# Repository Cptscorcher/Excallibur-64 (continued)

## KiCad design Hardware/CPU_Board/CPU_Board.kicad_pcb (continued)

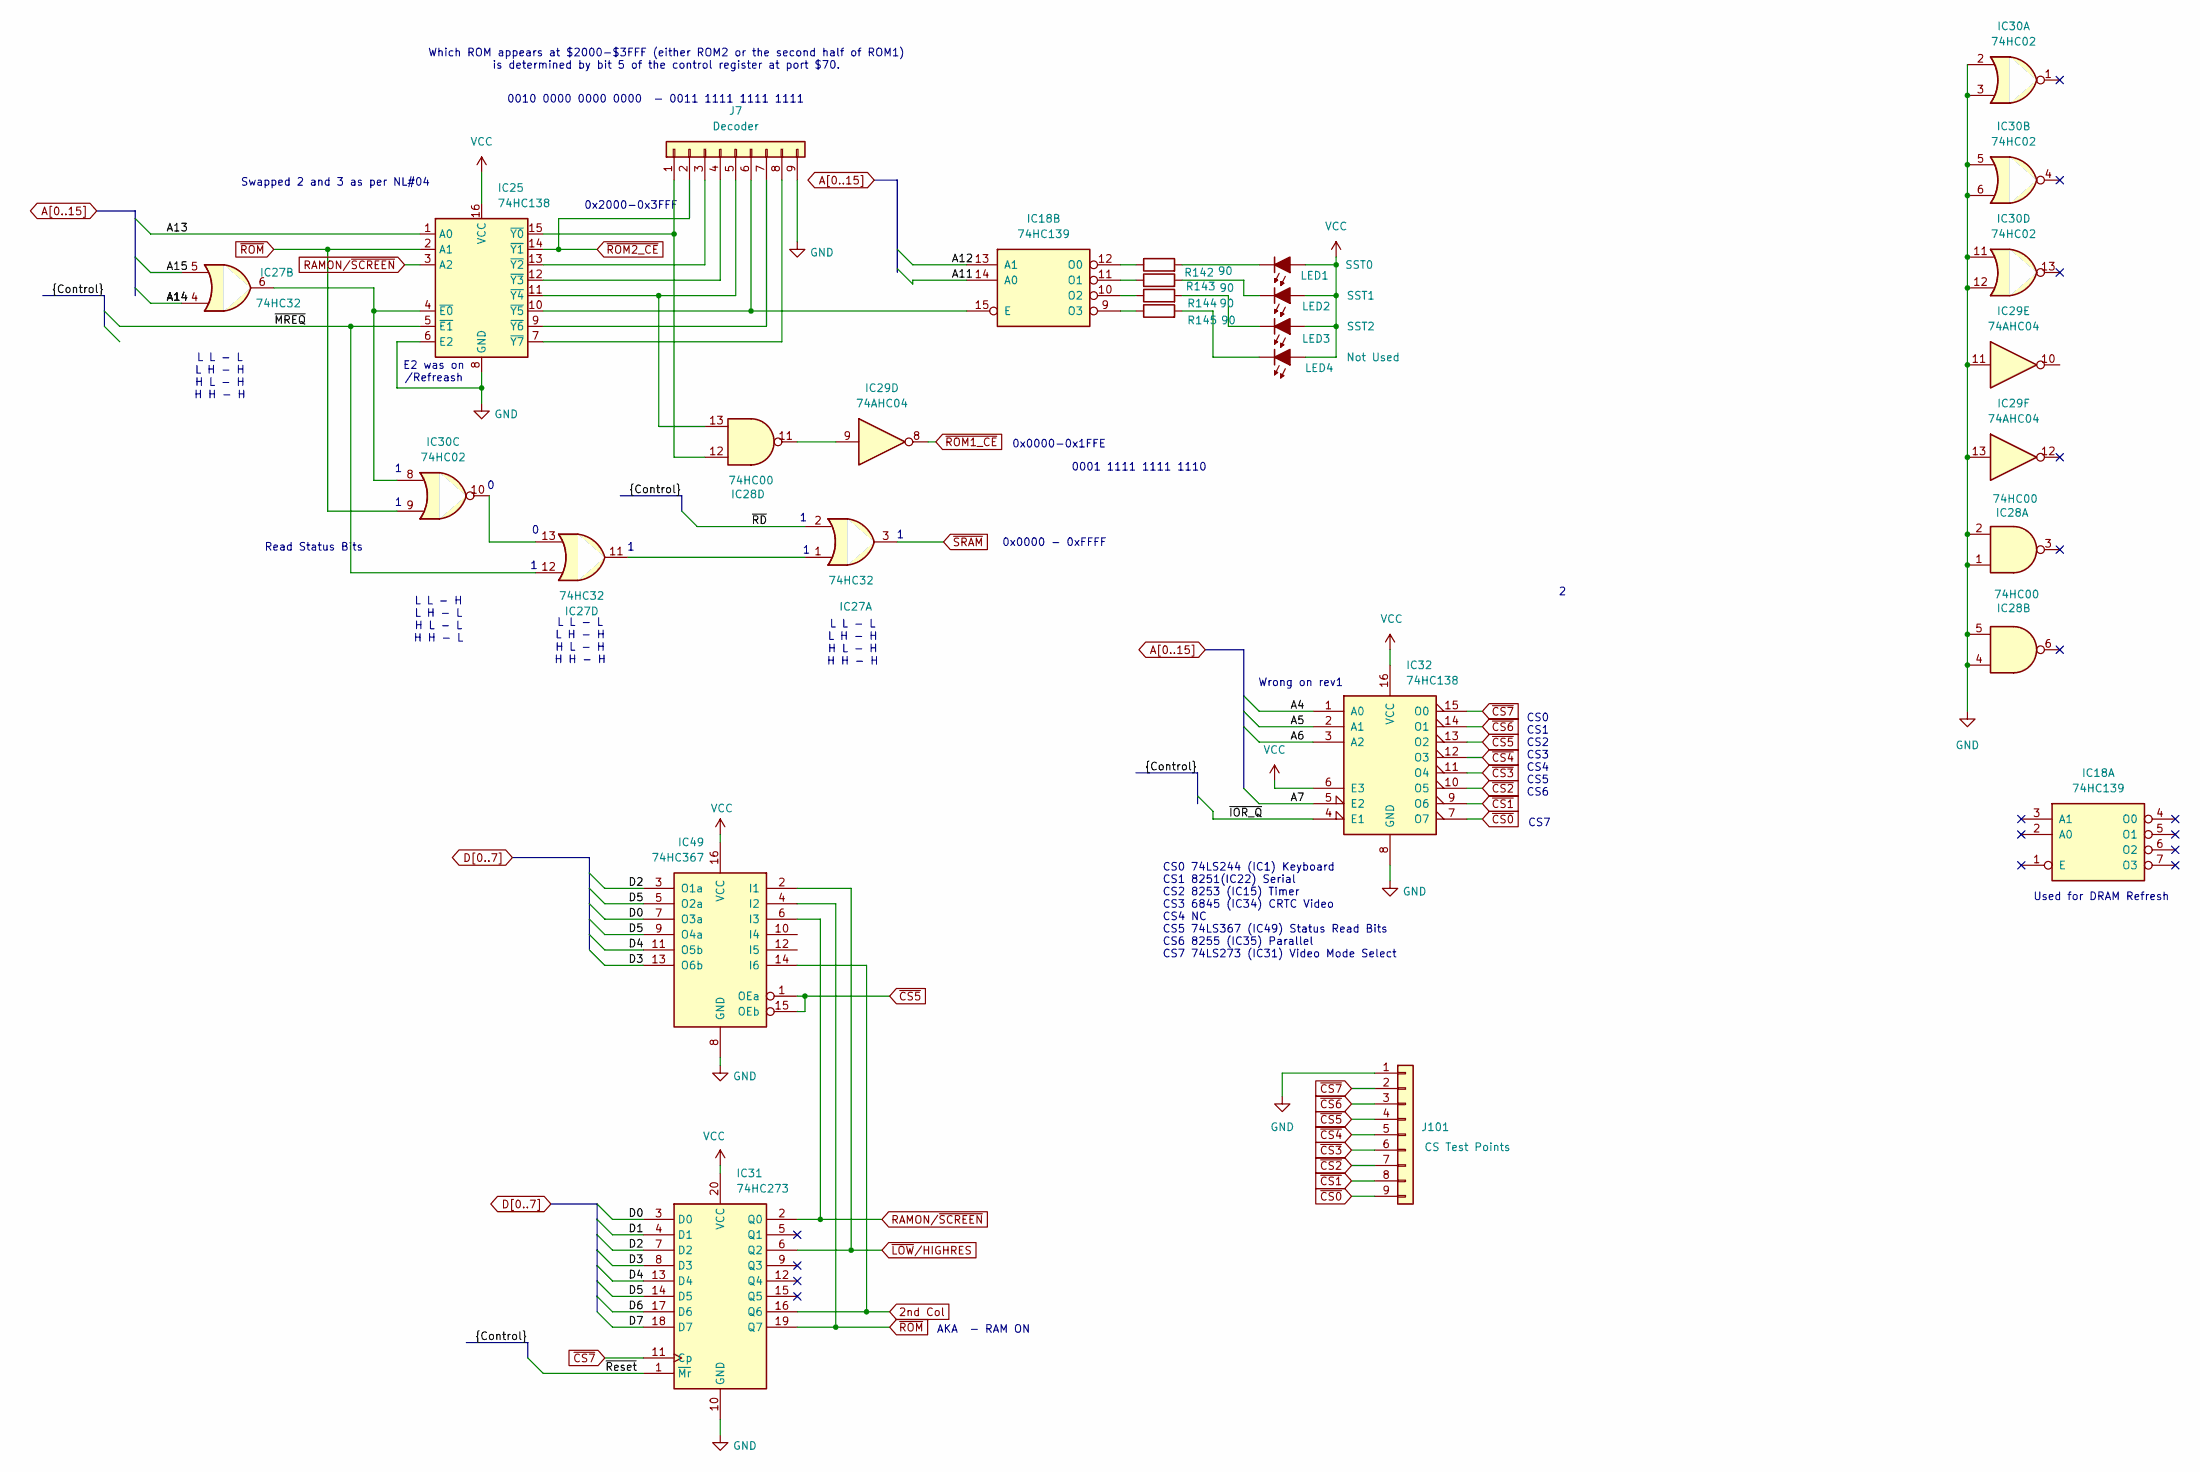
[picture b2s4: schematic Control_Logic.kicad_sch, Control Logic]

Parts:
IC18: 74HC139; DIP-16_W7.62mm_Socket_LongPads
IC25: 74HC138; DIP-16_W7.62mm_LongPads
IC27: 74HC32; DIP-14_W7.62mm_LongPads
IC28: 74HC00; DIP-14_W7.62mm_LongPads
IC29: 74AHC04; DIP-14_W7.62mm_Socket_LongPads
IC30: 74HC02; DIP-14_W7.62mm_LongPads
IC31: 74HC273; DIP-20_W7.62mm_Socket
IC32: 74HC138; DIP-16_W7.62mm_Socket_LongPads
IC49: 74HC367; DIP-16_W7.62mm_Socket_LongPads
J7: Decoder; PinHeader_1x09_P2.54mm_Vertical
J101: CS Test Points; PinHeader_1x09_P2.54mm_Vertical
LED1: SST0; LED_1206_3216Metric
LED2: SST1; LED_1206_3216Metric
LED3: SST2; LED_1206_3216Metric
LED4: Not Used; LED_1206_3216Metric
R142, R143, R144, R145: 90; R_1206_3216Metric_Pad1.30x1.75mm_HandSolder

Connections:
2nd Col: IC31.16 (Q6), IC49.14 (I6)
/Control_logic/~IOR_Q: IC32.4 (E1)
/Control_logic/~MREQ: IC25.5 (~E1), IC27.12
/Control_logic/~RD: IC27.2
/Control_logic/~Reset: IC31.1 (~Mr)
A4: IC32.1 (A0); also elsewhere on the board
A5: IC32.2 (A1); also elsewhere on the board
A6: IC32.3 (A2); also elsewhere on the board
A7: IC32.5 (E2); also elsewhere on the board
A11: IC18.14 (A0); also elsewhere on the board
A12: IC18.13 (A1); also elsewhere on the board
A13: IC25.1 (A0); also elsewhere on the board
A15: IC27.5; also elsewhere on the board
D0: IC31.3 (D0), IC49.7 (O3a); also elsewhere on the board
D1: IC31.4 (D1); also elsewhere on the board
D2: IC31.7 (D2), IC49.3 (O1a); also elsewhere on the board
D3: IC31.8 (D3), IC49.13 (O6b); also elsewhere on the board
D4: IC31.13 (D4), IC49.11 (O5b); also elsewhere on the board
D5: IC31.14 (D5), IC49.5 (O2a), IC49.9 (O4a); also elsewhere on the board
D6: IC31.17 (D6); also elsewhere on the board
D7: IC31.18 (D7); also elsewhere on the board
unnamed: IC18.15 (E), IC25.10 (~Y5), J7.6
unnamed: IC18.12 (O0), R142.1
unnamed: IC18.11 (O1), R143.1
unnamed: IC18.10 (O2), R144.1
unnamed: IC18.9 (O3), R145.1
unnamed: IC25.4 (~E0), IC27.6, IC30.8
unnamed: IC25.15 (~Y0), IC28.12, J7.1
unnamed: IC25.13 (~Y2), J7.3
unnamed: IC25.12 (~Y3), J7.4
unnamed: IC25.11 (~Y4), IC28.13, J7.5
unnamed: IC25.9 (~Y6), J7.7
unnamed: IC25.7 (~Y7), J7.8
unnamed: IC27.1, IC27.11
unnamed: IC27.13, IC30.10
unnamed: IC28.11, IC29.9
unnamed: LED1.1 (K), R142.2
unnamed: LED2.1 (K), R143.2
unnamed: LED3.1 (K), R144.2
unnamed: LED4.1 (K), R145.2
RAMON/~SCREEN: IC25.3 (A2), IC31.2 (Q0), IC49.6 (I3); also elsewhere on the board
VCC: IC25.16 (VCC), IC31.20 (VCC), IC32.6 (E3), IC32.16 (VCC), IC49.16 (VCC), LED1.2 (A), LED2.2 (A), LED3.2 (A), LED4.2 (A); also elsewhere on the board
~CS0: IC32.7 (O7), J101.9; also elsewhere on the board
~CS1: IC32.9 (O6), J101.8; also elsewhere on the board
~CS2: IC32.10 (O5), J101.7; also elsewhere on the board
~CS3: IC32.11 (O4), J101.6
~CS4: IC32.12 (O3), J101.5
~CS5: IC32.13 (O2), IC49.1 (OEa), IC49.15 (OEb), J101.4
~CS6: IC32.14 (O1), J101.3; also elsewhere on the board
~CS7: IC31.11 (Cp), IC32.15 (O0), J101.2
~LOW/HIGHRES: IC31.6 (Q2), IC49.2 (I1)
~ROM1_CE: IC29.8; also elsewhere on the board
~ROM2_CE: IC25.14 (~Y1), J7.2; also elsewhere on the board
~ROM: IC25.2 (A1), IC30.9, IC31.19 (Q7), IC49.4 (I2)
~SRAM: IC27.3; also elsewhere on the board

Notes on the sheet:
Read Status Bits
Wrong on rev1
L L - H L H - L H L - L H H - L
L L - L L H - H H L - H H H - H
0001 1111 1111 1110
0x0000-0x1FFE
Used for DRAM Refresh
0x0000 - 0xFFFF
E2 was on /Refreash
CS0 74LS244 (IC1) Keyboard CS1 8251(IC22) Serial CS2 8253 (IC15) Timer CS3 6845 (IC34) CRTC Video CS4 NC CS5 74LS367 (IC49) Status Read Bits CS6 8255 (IC35) Parallel CS7 74LS273 (IC31) Video Mode Select
Swapped 2 and 3 as per NL#04
CS0 CS1 CS2 CS3 CS4 CS5 CS6
CS7
Which ROM appears at $2000-$3FFF (either ROM2 or the second half of ROM1) is determined by bit 5 of the control register at port $70.
AKA - RAM ON
0010 0000 0000 0000 - 0011 1111 1111 1111
0x2000-0x3FFF

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
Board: 2 copper layers, 150 parts (0 on the bottom side), 180 nets, no tracks yet.

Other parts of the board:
REF01, REF02, REF04, REF05, REF06: MountingHole_3.2mm_M3_DIN965_Pad
U101#2: 74AHCU04; DIP-14_W7.62mm_Socket_LongPads

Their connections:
/Power_Reset/~RESET: U101#2.10; also elsewhere on the board
VCC: U101#2.14 (VCC); also elsewhere on the board

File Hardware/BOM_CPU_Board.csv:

"Reference","Value","Qty","DNP"
"C7,C121,C123,C124,C125,C126","1uF","6",""
"C19,C101","4.7uF","2",""
"C25","56nF","1",""
"C26","10uF","1",""
"C102,C103,C104,C105,C106,C108,C109,C111,C112,C113,C114,C115,C116,C117,C118,C119,C120,C129,C130,C131","10nf","20",""
"C107,C128","33p","2",""
"C110","1000uF","1",""
"C122","100uF","1",""
"C127","100pf","1",""
"D1,D2,D3,D4,D5,D6,D7,D8,D21,D22,D104","1N4148","11",""
"D101","5v","1",""
"D102","1N4448","1",""
"D103","12v","1",""
"DZ101","BZX79-B2V4","1",""
"IC1","74HCT244","1",""
"IC15","8253","1",""
"IC16","Z84C00","1",""
"IC18","74HC139","1",""
"IC22","8251","1",""
"IC25,IC32","74HC138","2",""
"IC27","74HC32","1",""
"IC28","74HC00","1",""
"IC29","74HC04","1",""
"IC30","74HC02","1",""
"IC31","74HC273","1",""
"IC35","82C55A","1",""
"IC42","LM348N","1",""
"IC49","74HC367","1",""
"IC54","74HC123","1",""
"IC56","74HC161","1",""
"IC102","MAX232","1",""
"IC110","SST39SF010","1",""
"IC111","HM62256ALSP","1",""
"J3","Ext Clk","1",""
"J4","Expansion","1",""
"J7","Decoder","1",""
"J101","CS Test Points","1",""
"J102","Tx","1",""
"J103","Rx","1",""
"J104","SPEAKER (AUDIO)","1",""
"J105","TTL Serial","1",""
"J107","Power In","1",""
"J108","CASSETTE","1",""
"J109","RTS - DSR","1",""
"J110","PARALLEL OUTPUT PORT","1",""
"J111","Keyboard","1",""
"J112","Serial","1",""
"LED1","SST0","1",""
"LED2","SST1","1",""
"LED3","SST2","1",""
"LED4","Not Used","1",""
"LED101,LED103","Red","2",""
"LED102,LED104","Green","2",""
"Q1,Q102","BC548","2",""
"Q101","2N2222A-TO92","1",""
"R17,R104,R110,R112,R113,RN101","10K","6",""
"R18,R23,R25,R111","2K2","4",""
"R19,R21,R114","18K","3",""
"R20,R115","18","2",""
"R22,R105","1K","2",""
"R24","68K","1",""
"R28,R29,R30,R31","4k7","4",""
"R38","10","1",""
"R39","820","1",""
"R101","220","1",""
"R102","100K","1",""
"R103,R106,RN2","4K7","3",""
"R107","6K8","1",""
"R108,R109,R116,R117,R142,R143,R144,R145","90","8",""
"R118","560","1",""
"R119","360","1",""
"R120","1M","1",""
"SW101","Reset","1",""
"TP101,XTAL2","16Mhz","2",""
"TP102","TestPoint","1",""
"U101","74HC14","1",""
"U102","LM7805CT","1",""
"U103","LM7812CT","1",""

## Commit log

2025-05-22 Add files via upload
    Initial Commit
2025-05-30 Update README.md
    updated with more design info
2025-05-30 Add files via upload
    Updated to version 3. not yet built but fixes some issues that were with version 2. Will update again before it goes out for manufacture
2025-06-02 Fixed some issues with memory mapping IC 25
2025-06-02 Initial Commit
    Just some basic test files
2025-06-05 Fixing up broken libraries
    not all components updated yet but working through it to minimise dependences on 3rd party libraries. Still have a bunch of DRM repairs to do as well :(
2025-06-10 New PCB and library fixups
    fixed a bunch of 3rd party libraries that shouldn't be there and have done an initial PCB layout. Still using ver 2 for testing before committing to a new PCB
